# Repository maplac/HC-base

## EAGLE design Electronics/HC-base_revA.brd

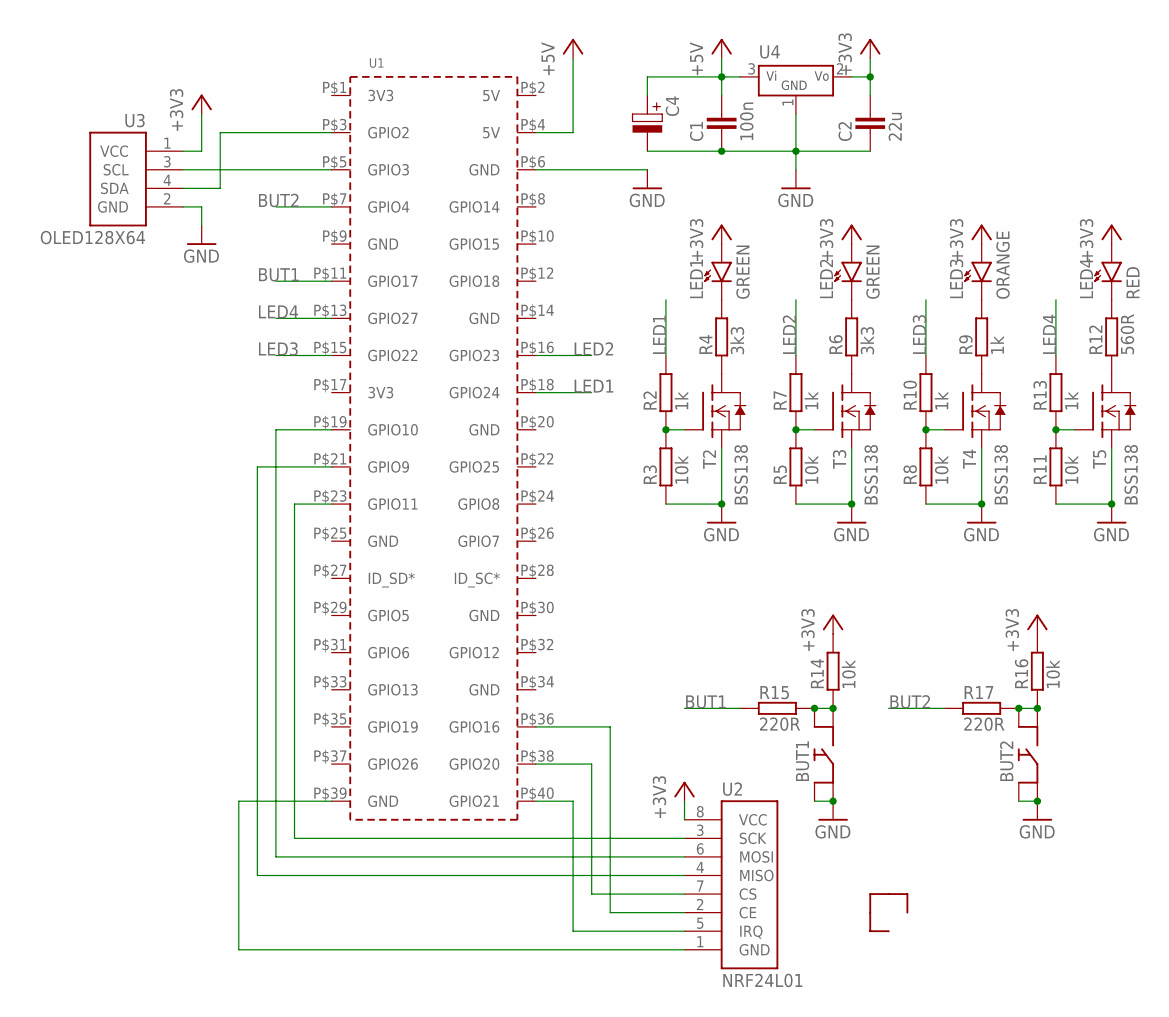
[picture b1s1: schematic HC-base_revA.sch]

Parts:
BUT1, BUT2: BUTTON'SMD'; BUTTON_SMD
C1: 100n; C0805
C2: 22u; C0805
C4: C-POLY'6.5MM'; ELYT-6MM5
LED1, LED2: GREEN; LED0805
LED3: ORANGE; LED0805
LED4: RED; LED0805
R2, R7, R9, R10, R13: 1k; R0805
R3, R5, R8, R11, R14, R16: 10k; R0805
R4, R6: 3k3; R0805
R12: 560R; R0805
R15, R17: 220R; R0805
T2, T3, T4, T5: BSS138; SOT23
U1: RPI3_SIMPLE'PART'; RPI3-PART
U2: NRF24L01
U3: OLED128X64
U4: V_STAB'TS1117'; SOT223
U$1, U$2, U$3: CORNER

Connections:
+3V3: C2.2, LED1.1 (A), LED2.1 (A), LED3.1 (A), LED4.1 (A), R14.2, R16.2, U2.8 (VCC), U3.1 (VCC), U4.2 (VOUT)
+5V: C1.2, C4.+ (POS), U1.P$4 (5V), U4.3 (VIN)
BUT1: R15.1, U1.P$11 (GPIO17)
BUT2: R17.1, U1.P$7 (GPIO4)
GND: BUT1.1 (4), BUT1.2, BUT2.1 (4), BUT2.2, C1.1, C2.1, C4.- (NEG), R3.1, R5.1, R8.1, R11.1, T2.2 (S), T3.2 (S), T4.2 (S), T5.2 (S), U1.P$6 (GND), U3.2 (GND), U4.1 (GND)
LED1: R2.2, U1.P$18 (GPIO24)
LED2: R7.2, U1.P$16 (GPIO23)
LED3: R10.2, U1.P$15 (GPIO22)
LED4: R13.2, U1.P$13 (GPIO27)
unnamed: R2.1, R3.2, T2.1 (G)
unnamed: U1.P$23 (GPIO11), U2.3 (SCK)
unnamed: U1.P$19 (GPIO10), U2.6 (MOSI)
unnamed: U1.P$21 (GPIO9), U2.4 (MISO)
unnamed: U1.P$38 (GPIO20), U2.7 (CS)
unnamed: U1.P$36 (GPIO16), U2.2 (CE)
unnamed: U1.P$40 (GPIO21), U2.5 (IRQ)
unnamed: U1.P$3 (GPIO2), U3.4 (SDA)
unnamed: U1.P$5 (GPIO3), U3.3 (SCL)
unnamed: R4.1, T2.3 (D)
unnamed: R6.1, T3.3 (D)
unnamed: R9.1, T4.3 (D)
unnamed: R12.1, T5.3 (D)
unnamed: R5.2, R7.1, T3.1 (G)
unnamed: LED1.2 (K), R4.2
unnamed: LED2.2 (K), R6.2
unnamed: R8.2, R10.1, T4.1 (G)
unnamed: LED3.2 (K), R9.2
unnamed: LED4.2 (K), R12.2
unnamed: R11.2, R13.1, T5.1 (G)
unnamed: U1.P$39 (GND), U2.1 (GND)
unnamed: BUT1.3 (1), BUT1.4 (3), R14.1, R15.2
unnamed: BUT2.3 (1), BUT2.4 (3), R16.1, R17.2

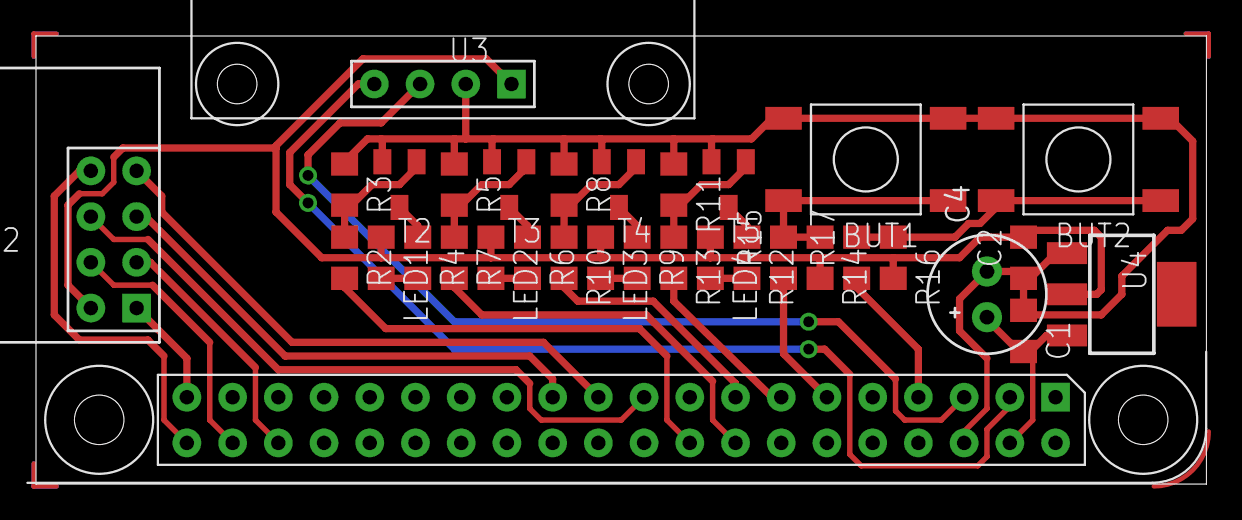
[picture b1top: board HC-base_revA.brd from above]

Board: 2 copper layers, 65.0 x 24.9 mm, 36 parts (0 on the bottom side), 32 nets.

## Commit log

2018-03-17 added: circuit diagram and pcb
2018-03-18 modified: diagram and pcb
2018-03-21 added: exported files for manufacturing the PCB
2018-03-21 modified: finished PCB
2018-03-30 added: pictures of finished board
